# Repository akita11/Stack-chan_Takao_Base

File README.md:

# Stack-chan_Takao_Base

現時点で ｽﾀｯｸﾁｬﾝ を組み立てる最もシンプルな方法と思われる、[タカオさん](https://twitter.com/mongonta555)の[タカオ版（旧称：GoBottom版）](https://mongonta.booth.pm/)のための、M5Stack本体と2個のサーボモータ、給電用のUSB TypeCコネクタがついたボードです。電源スイッチもついています。まるごと一式、タカオ版のサーボ固定部分(Bracket)に収納できます。市販のUSB Type-CコネクタつきのACアダプタ等をつないで給電して使用します。以下のように、本体の後ろ側からUSB Type-Cケーブルで給電して動作させることができます。

## 表面実装部品版

※[完成品としてスイッチサイエンスで委託販売中](https://www.switch-science.com/products/8905)です

## 挿入実装部品版

※[部品キットとしてスイッチサイエンスで委託販売中](https://www.switch-science.com/products/8906)です

※部品キット版では、[作り方](https://github.com/akita11/Stack-chan_Takao_Base/blob/main/Build/README.md)の手順で部品をはんだ付けしてください。

## 他に用意するもの

- M5Stack本体 (Core BasicまたはCore2がおすすめ）
- サーボモータ2個 ([FS90MG](https://www.switch-science.com/products/8041)や[M5Stack ServoKit 180deg](https://www.switch-science.com/products/6478)、[SG90](https://akizukidenshi.com/catalog/g/gM-08761/)など)
- Groveケーブル ([M5Stack用5cm](https://www.switch-science.com/products/8664)など。すでにM5StackのUNITなどで余っているものがあればそれでもOK）
- ["タカオ版（旧称：GoBottom版）"の筐体一式](https://mongonta.booth.pm/)、または[それの3Dデータ](https://github.com/meganetaaan/stack-chan/tree/dev/v1.0/case/contributed/mongonta_case_for_SG90_and_M5GoBottomBoard)を3Dプリント出力したものと必要なネジ類

## 使い方

- 筐体の組み立てなどは、[タカオさんの手順](https://raspberrypi.mongonta.com/how-to-build-easy-stackchan-m5gobottom/)を参考に行います。
- M5Stack本体と本ボードはGroveケーブルで接続します
- 2個のサーボを本ボードに接続します。ボード上の「H1」側には水平方向（足側）のサーボを、「V2」側には上下方向（筐体側）のサーボを接続します。いずれも、サーボのGND側（茶色や黒のケーブル側）を、本ボードの端側（白マークのある側）に挿し込みます。
- 本ボードを、Bracket（サーボを固定している部品）に収めます。必要に応じて両面テープやネジなどで固定してください。

## うまく動作しないときは・・・

「バッテリをはずしたCore2にこのボードとサーボを接続し、Core2側にUSBケーブルをつないでプログラムの書き込みを行う」場合に、Core2が起動しない、またはリセット・再起動を繰り返す、という現象があるようです。その場合は、いったんGroveケーブルをはずしてCore2単体でプログラムを書き込んでから、このボードのUSBコネクタ（本体背面）から電源を供給して使用してください。

## おまけ：本ボードを作りたい人は・・・

- 基板を製造します (ガーバーデータ=Stack-chan_Takao_Base_gerber.zip)
- 部品を用意します（部品リスト=Stack-chan_Takao_Base_BOM.csv) 主な部品は秋月電子で購入できます。USBコネクタのみ、[AliExpress](https://ja.aliexpress.com/item/1005004175942555.html)などから購入します（汎用品のようで、互換の製品が多数あります）

  - 挿入実装版（はんだ付けに自信のない方向け）: 抵抗とコンデンサはC1, C2, R3,R4を使います。
  - 表面実装版（はんだ付けに自信のある方向け）: 抵抗とコンデンサはC3, C4, R1,R2を使います。

## Author

Junichi Akita (akita@ifdl.jp, @akita11)

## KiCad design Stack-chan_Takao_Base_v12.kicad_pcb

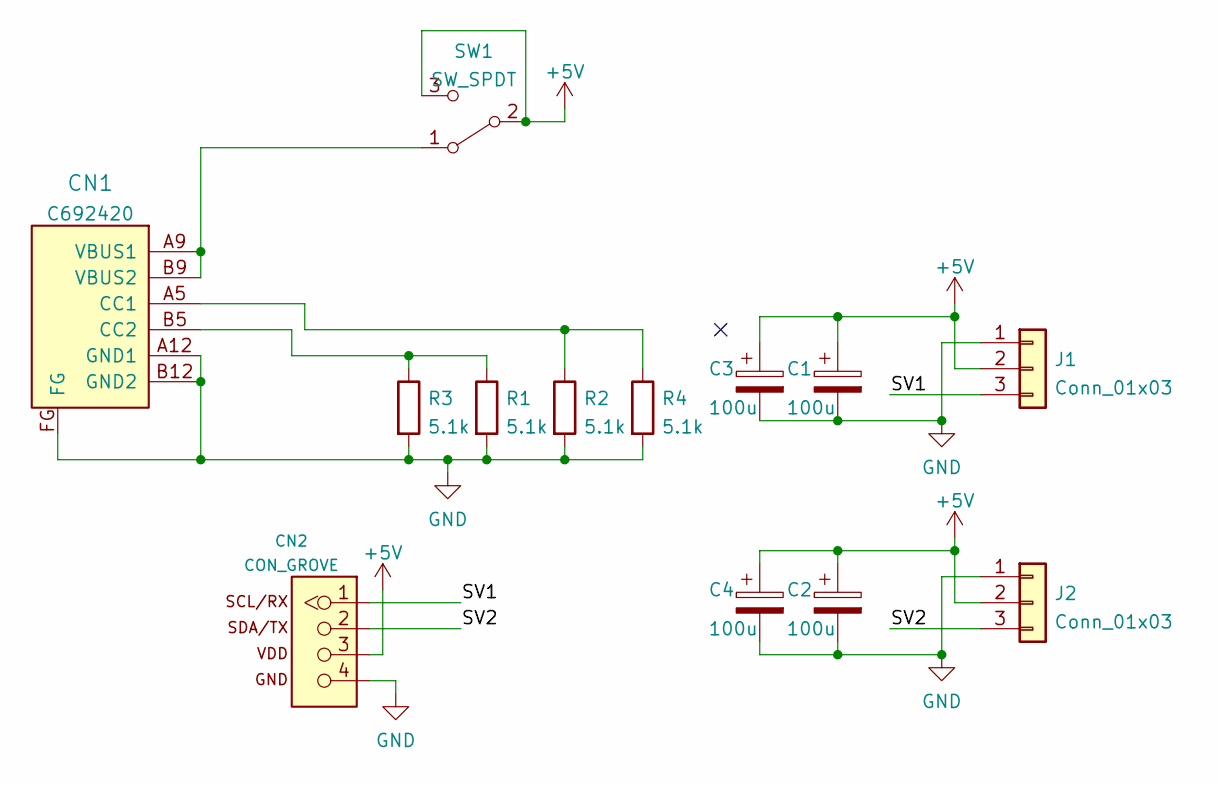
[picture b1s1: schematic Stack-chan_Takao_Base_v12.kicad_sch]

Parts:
C1, C2: 100u; CP_Radial_D6.3mm_P2.50mm
C3, C4: 100u; C_1206_3216Metric
CN1: CON_USB-C-6; USB-C_6P_V_TH; LCSC C692420
CN2: CON_GROVE; CON_GROVE_V
J1, J2: Conn_01x03; PinHeader_1x03_P2.54mm_Vertical
R1, R2: 5.1k; R_0603_1608Metric
R3, R4: 5.1k; R_Axial_DIN0204_L3.6mm_D1.6mm_P7.62mm_Horizontal
SW1: SW_SPDT; SW_SPDT_9x4mm_W2.5mm

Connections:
+5V: C1.1, C2.1, C3.1, C4.1, CN2.3, J1.2, J2.2, SW1.2 (B), SW1.3 (C)
/SV1: CN2.1, J1.3
/SV2: CN2.2, J2.3
GND: C1.2, C2.2, C3.2, C4.2, CN1.A12 (GND1), CN1.B12 (GND2), CN1.FG, CN2.4, J1.1, J2.1, R1.2, R2.2, R3.2, R4.2
unnamed: CN1.B5 (CC2), R1.1, R3.1
unnamed: CN1.A5 (CC1), R2.1, R4.1
unnamed: CN1.A9 (VBUS1), CN1.B9 (VBUS2), SW1.1 (A)

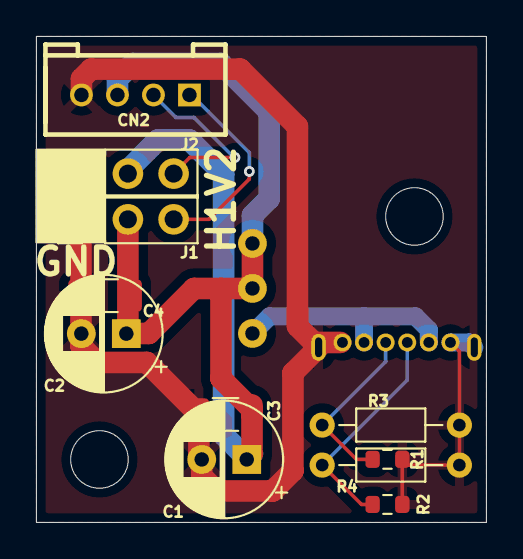
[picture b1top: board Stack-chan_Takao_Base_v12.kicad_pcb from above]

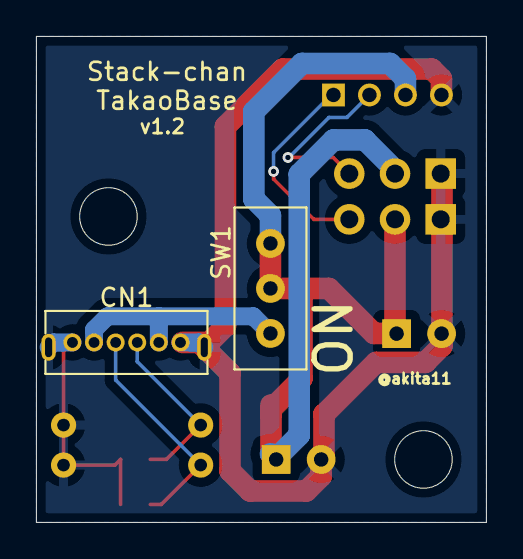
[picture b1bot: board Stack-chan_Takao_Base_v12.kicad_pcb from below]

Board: 2 copper layers, 25.0 x 27.0 mm, 13 parts (2 on the bottom side), 7 nets.

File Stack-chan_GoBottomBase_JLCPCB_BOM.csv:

Designator,Footprint,Quantity,Value,LCSC Part #
"C3, C4",C_1206_3216Metric,2,100u,C312983
"CN1, CN3",USB-C_16p_V_TH,2,CON_USB-C-16p, C2848615
CN2,CON_GROVE_V,1,CON_GROVE,C2845462
"J1, J2",PinHeader_1x03_P2.54mm_Vertical,2,Conn_01x03,C429954
"R1, R2",R_0603_1608Metric,2,5.1k,C23186

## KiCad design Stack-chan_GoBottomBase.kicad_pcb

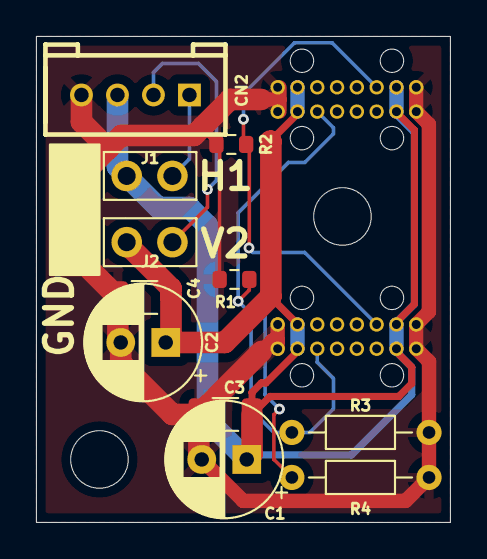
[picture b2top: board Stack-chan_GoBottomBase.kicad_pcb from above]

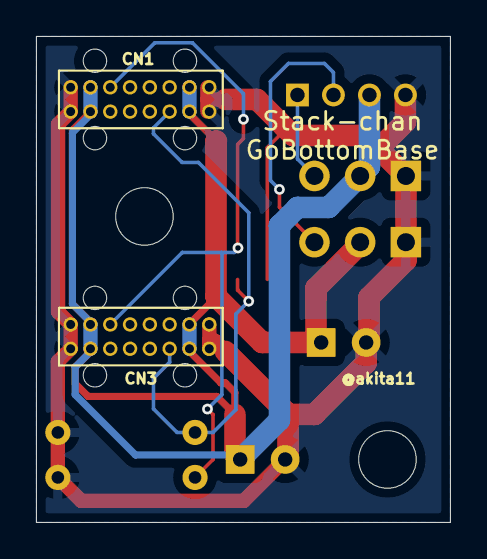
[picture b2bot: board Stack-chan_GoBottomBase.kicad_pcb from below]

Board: 2 copper layers, 23.0 x 27.0 mm, 13 parts (2 on the bottom side), 6 nets.

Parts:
C1, C2: 100u; CP_Radial_D6.3mm_P2.50mm
C3, C4: 100u; C_1206_3216Metric
CN1, CN3: CON_USB-C-16p; USB-C_16p_V_TH
CN2: CON_GROVE; CON_GROVE_V
J1, J2: Conn_01x03; PinHeader_1x03_P2.54mm_Vertical
R1, R2: 5.1k; R_0603_1608Metric
R3, R4: 5.1k; R_Axial_DIN0204_L3.6mm_D1.6mm_P7.62mm_Horizontal

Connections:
+5V: C1.1, C2.1, C3.1, C4.1, CN1.A4 (VBUS1), CN1.A9 (VBUS2), CN1.B4 (VBUS3), CN1.B9 (VBUS4), CN2.3, CN3.A4 (VBUS1), CN3.A9 (VBUS2), CN3.B4 (VBUS3), CN3.B9 (VBUS4), J1.2, J2.2
/SV1: CN2.1, J1.3
/SV2: CN2.2, J2.3
GND: C1.2, C2.2, C3.2, C4.2, CN1.A1 (GND1), CN1.A12 (GND2), CN1.B1 (GND3), CN1.B12 (GND4), CN2.4, CN3.A1 (GND1), CN3.A12 (GND2), CN3.B1 (GND3), CN3.B12 (GND4), J1.1, J2.1, R1.2, R2.2, R3.2, R4.2
unnamed: CN1.A5 (CC1), CN3.A5 (CC1), R2.1, R4.1
unnamed: CN1.B5 (CC2), CN3.B5 (CC2), R1.1, R3.1

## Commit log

2023-04-03 add servo info
2023-04-08 for v1
2023-04-08 fix typo
2023-04-09 rename
2023-04-15 add photo and Build instruction
2023-04-15 fix photo size
2023-04-15 update README, powering
2023-04-21 add reset problem
2023-05-11 update for v12/v121
2023-05-11 filename fix
2023-05-11 add SS link
2023-05-15 add usage photo
2023-05-15 fix filename typo
